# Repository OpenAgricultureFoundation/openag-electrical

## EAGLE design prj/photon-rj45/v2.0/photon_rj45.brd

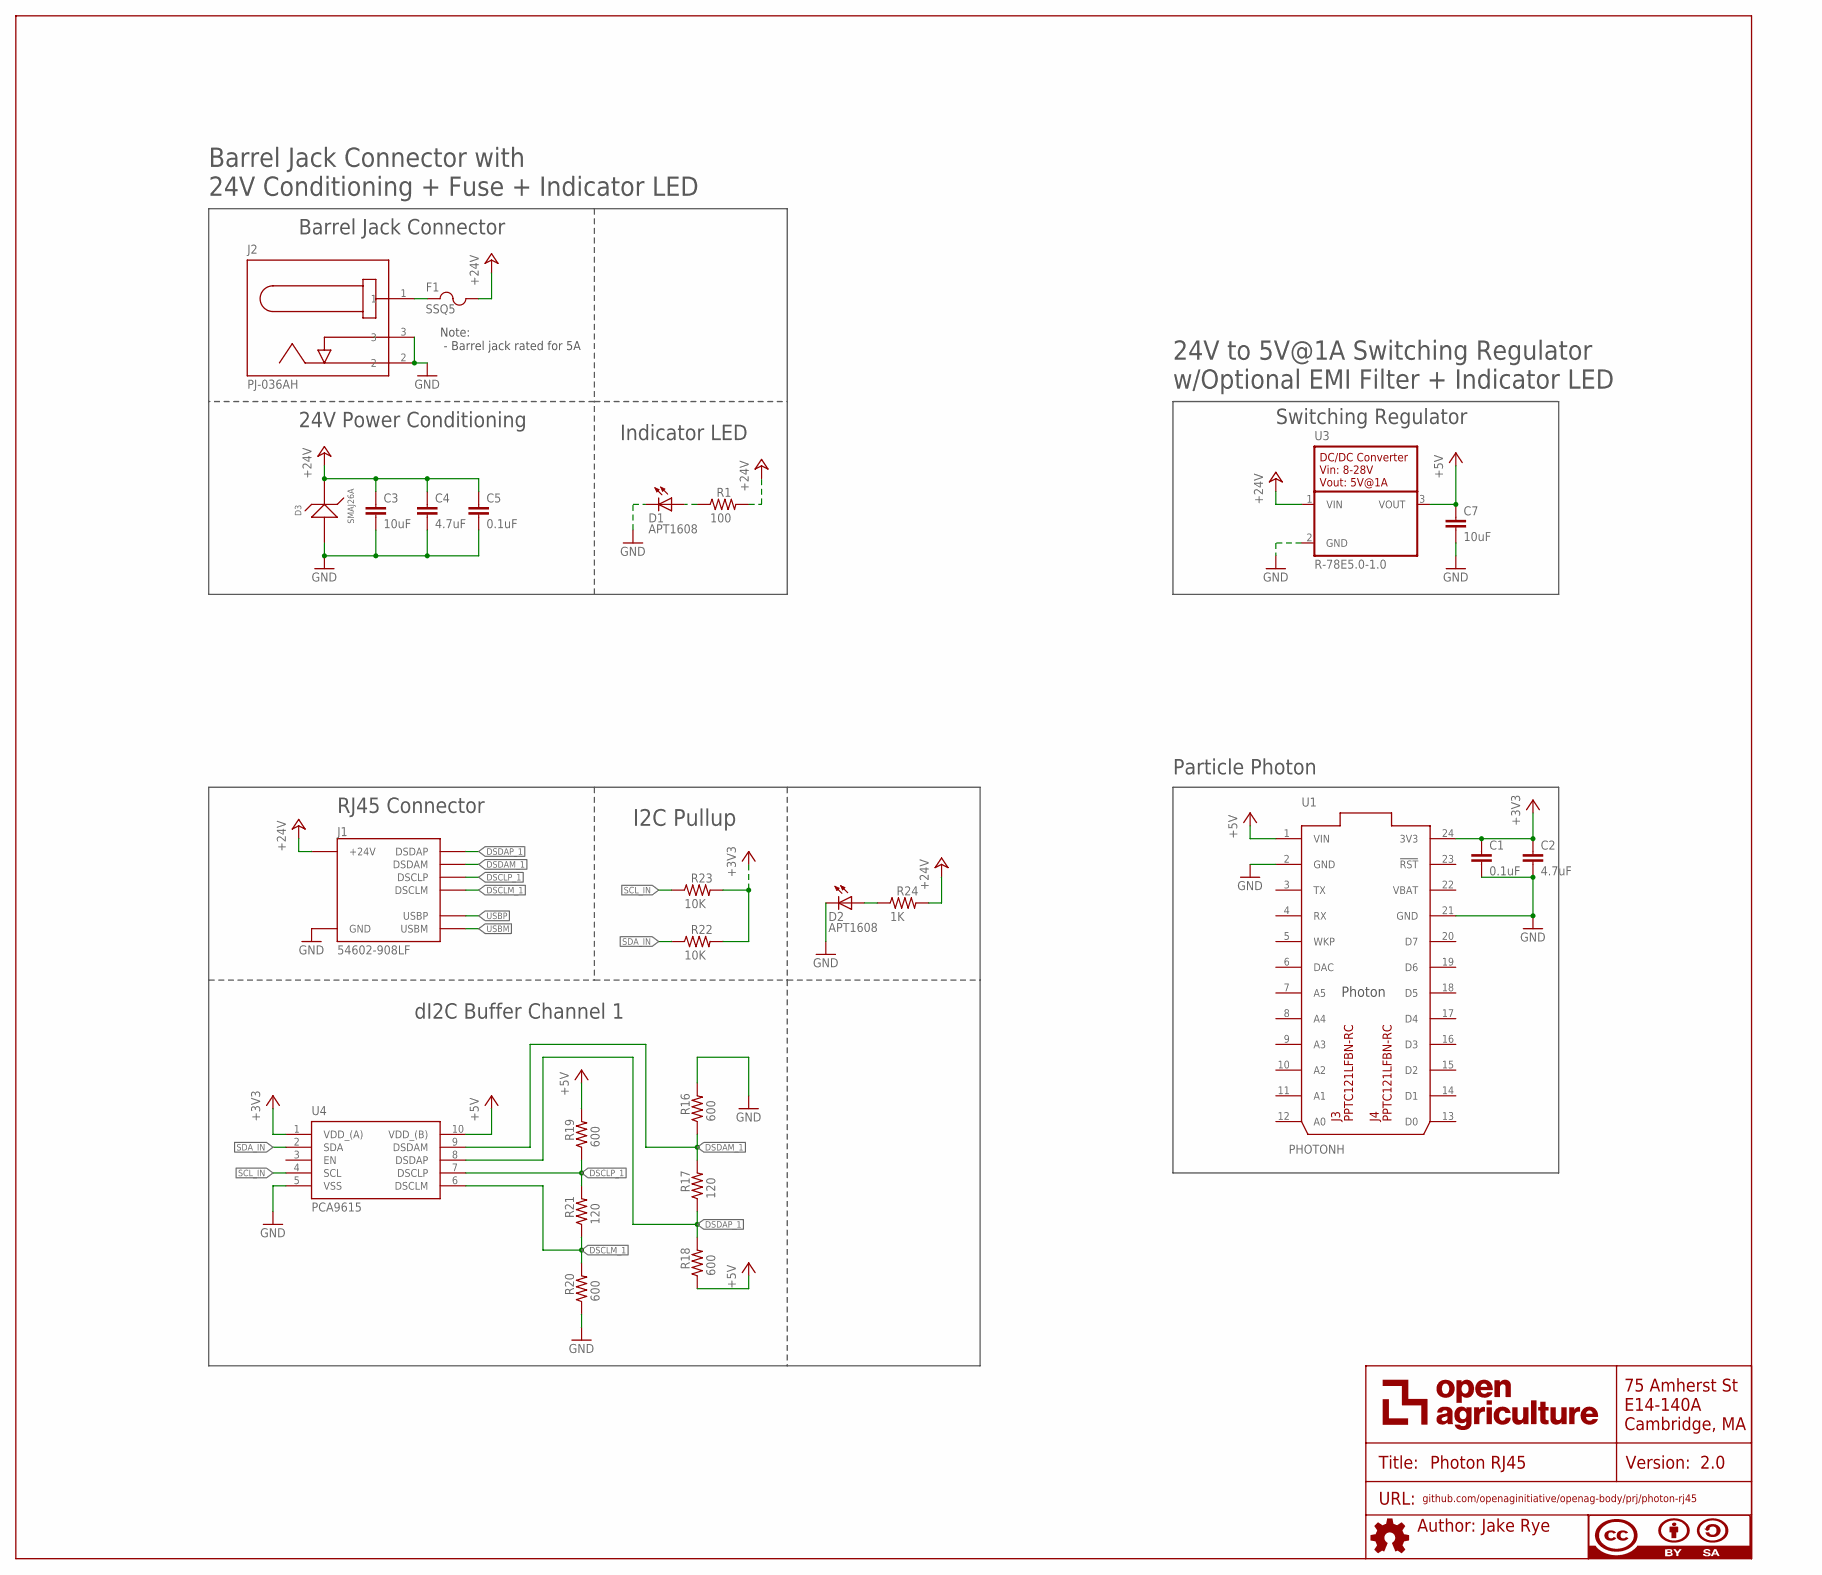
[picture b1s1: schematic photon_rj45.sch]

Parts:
C1, C5: 0.1uF; C0603
C2, C4: 4.7uF; C0805
C3, C7: 10uF; C0805
D1, D2: APT1608; CHIPLED_0603
D3: SMAJ26A; SMA
F1: SSQ5; SS
J1: 54602-908LF; RJ45-DI2C-USB-54602-908LF
J2: PJ-036AH; BARREL-JACK-PJ-036AH
J3, J4: PPTC121LFBN-RC; NAME-VALUE-ONLY
R1: 100; RC0603N
R16, R18, R19, R20: 600; RC0603N
R17, R21: 120; RC0603N
R22, R23: 10K; RC0603N
R24: 1K; RC0603N
U1: PHOTONH; PHOTON-NO-BOTTOM-LABELS
U3: R-78E5.0-1.0
U4: PCA9615; SOP50P490X110-10N

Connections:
24V_IN1: F1.1, J2.1
+3V3: C1.1, C2.1, R22.2, R23.2, U1.24 (3V3), U4.1 (VDD_(A))
+5V: C7.1, R18.1, R19.2, U1.1 (VIN), U3.3 (VOUT), U4.10 (VDD_(B))
+24V: C3.1, C4.1, C5.1, D3.1, F1.2, J1.24V(6) (+24V), R1.2, R24.2, U3.1 (VIN)
DSCLM_1: J1.DSCLM(5) (DSCLM), R20.2, R21.1, U4.6 (DSCLM)
DSCLP_1: J1.DSCLP(4) (DSCLP), R19.1, R21.2, U4.7 (DSCLP)
DSDAM_1: J1.DSDAM(2) (DSDAM), R16.1, R17.2, U4.9 (DSDAM)
DSDAP_1: J1.DSDAP(1) (DSDAP), R17.1, R18.2, U4.8 (DSDAP)
GND: C1.2, C2.2, C3.2, C4.2, C5.2, C7.2, D1.C, D2.C, D3.2, J1.GND(3) (GND), J2.2, J2.3, R16.2, R20.1, U1.2 (GND), U1.21 (GND), U3.2 (GND), U4.5 (VSS)
unnamed: D2.A, R24.1
unnamed: D1.A, R1.1
SCL_IN: R23.1, U4.4 (SCL)
SDA_IN: R22.1, U4.2 (SDA)
USBM: J1.USBM(8) (USBM)
USBP: J1.USBP(7) (USBP)
VBAT: U1.22 (VBAT)

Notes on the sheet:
dI2C Buffer Channel 1
RJ45 Connector
I2C Pullup
Barrel Jack Connector
Barrel Jack Connector with 24V Conditioning + Fuse + Indicator LED
24V Power Conditioning
Indicator LED
Note: - Barrel jack rated for 5A
24V to 5V@1A Switching Regulator w/Optional EMI Filter + Indicator LED
Switching Regulator
Particle Photon

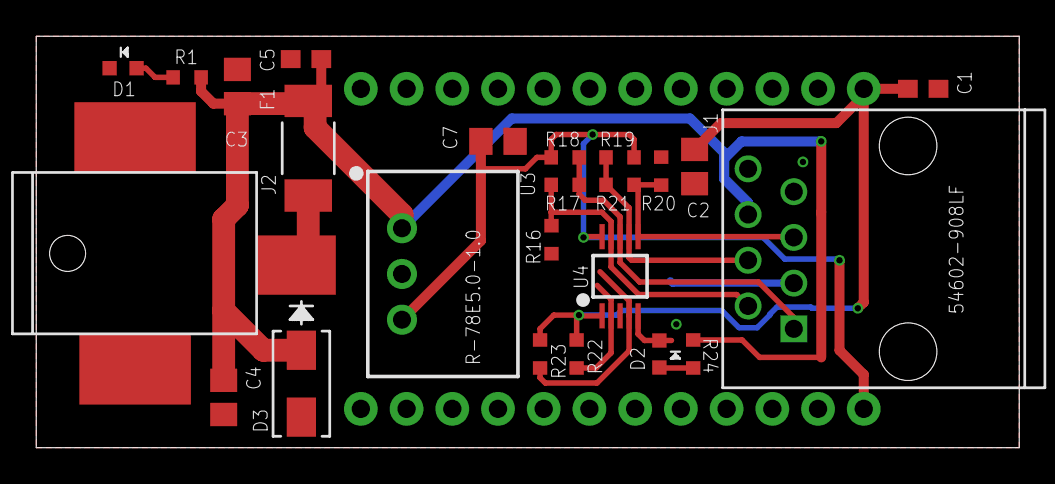
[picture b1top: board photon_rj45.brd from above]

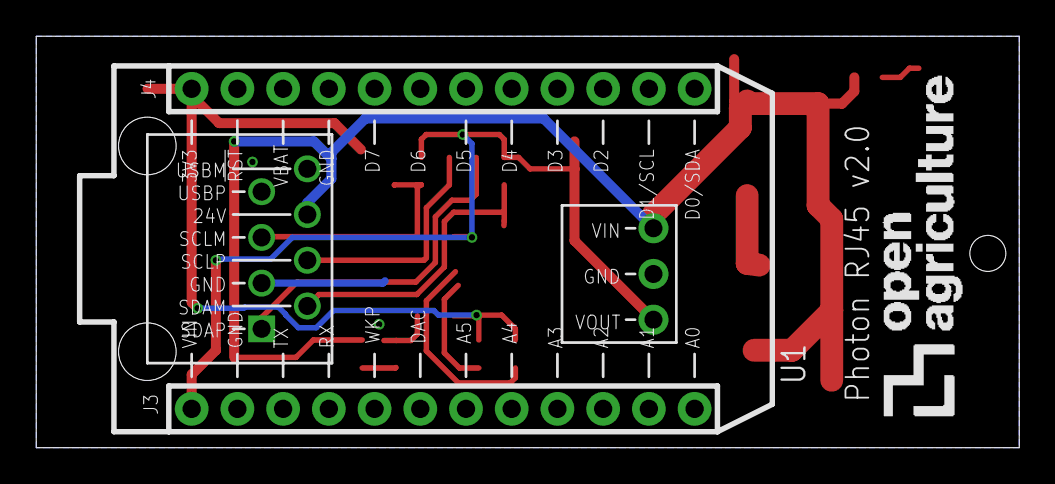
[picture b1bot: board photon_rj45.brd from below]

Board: 2 copper layers, 54.6 x 22.9 mm, 28 parts (4 on the bottom side), 13 nets.

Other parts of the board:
U$1: LOGO-BARE-750

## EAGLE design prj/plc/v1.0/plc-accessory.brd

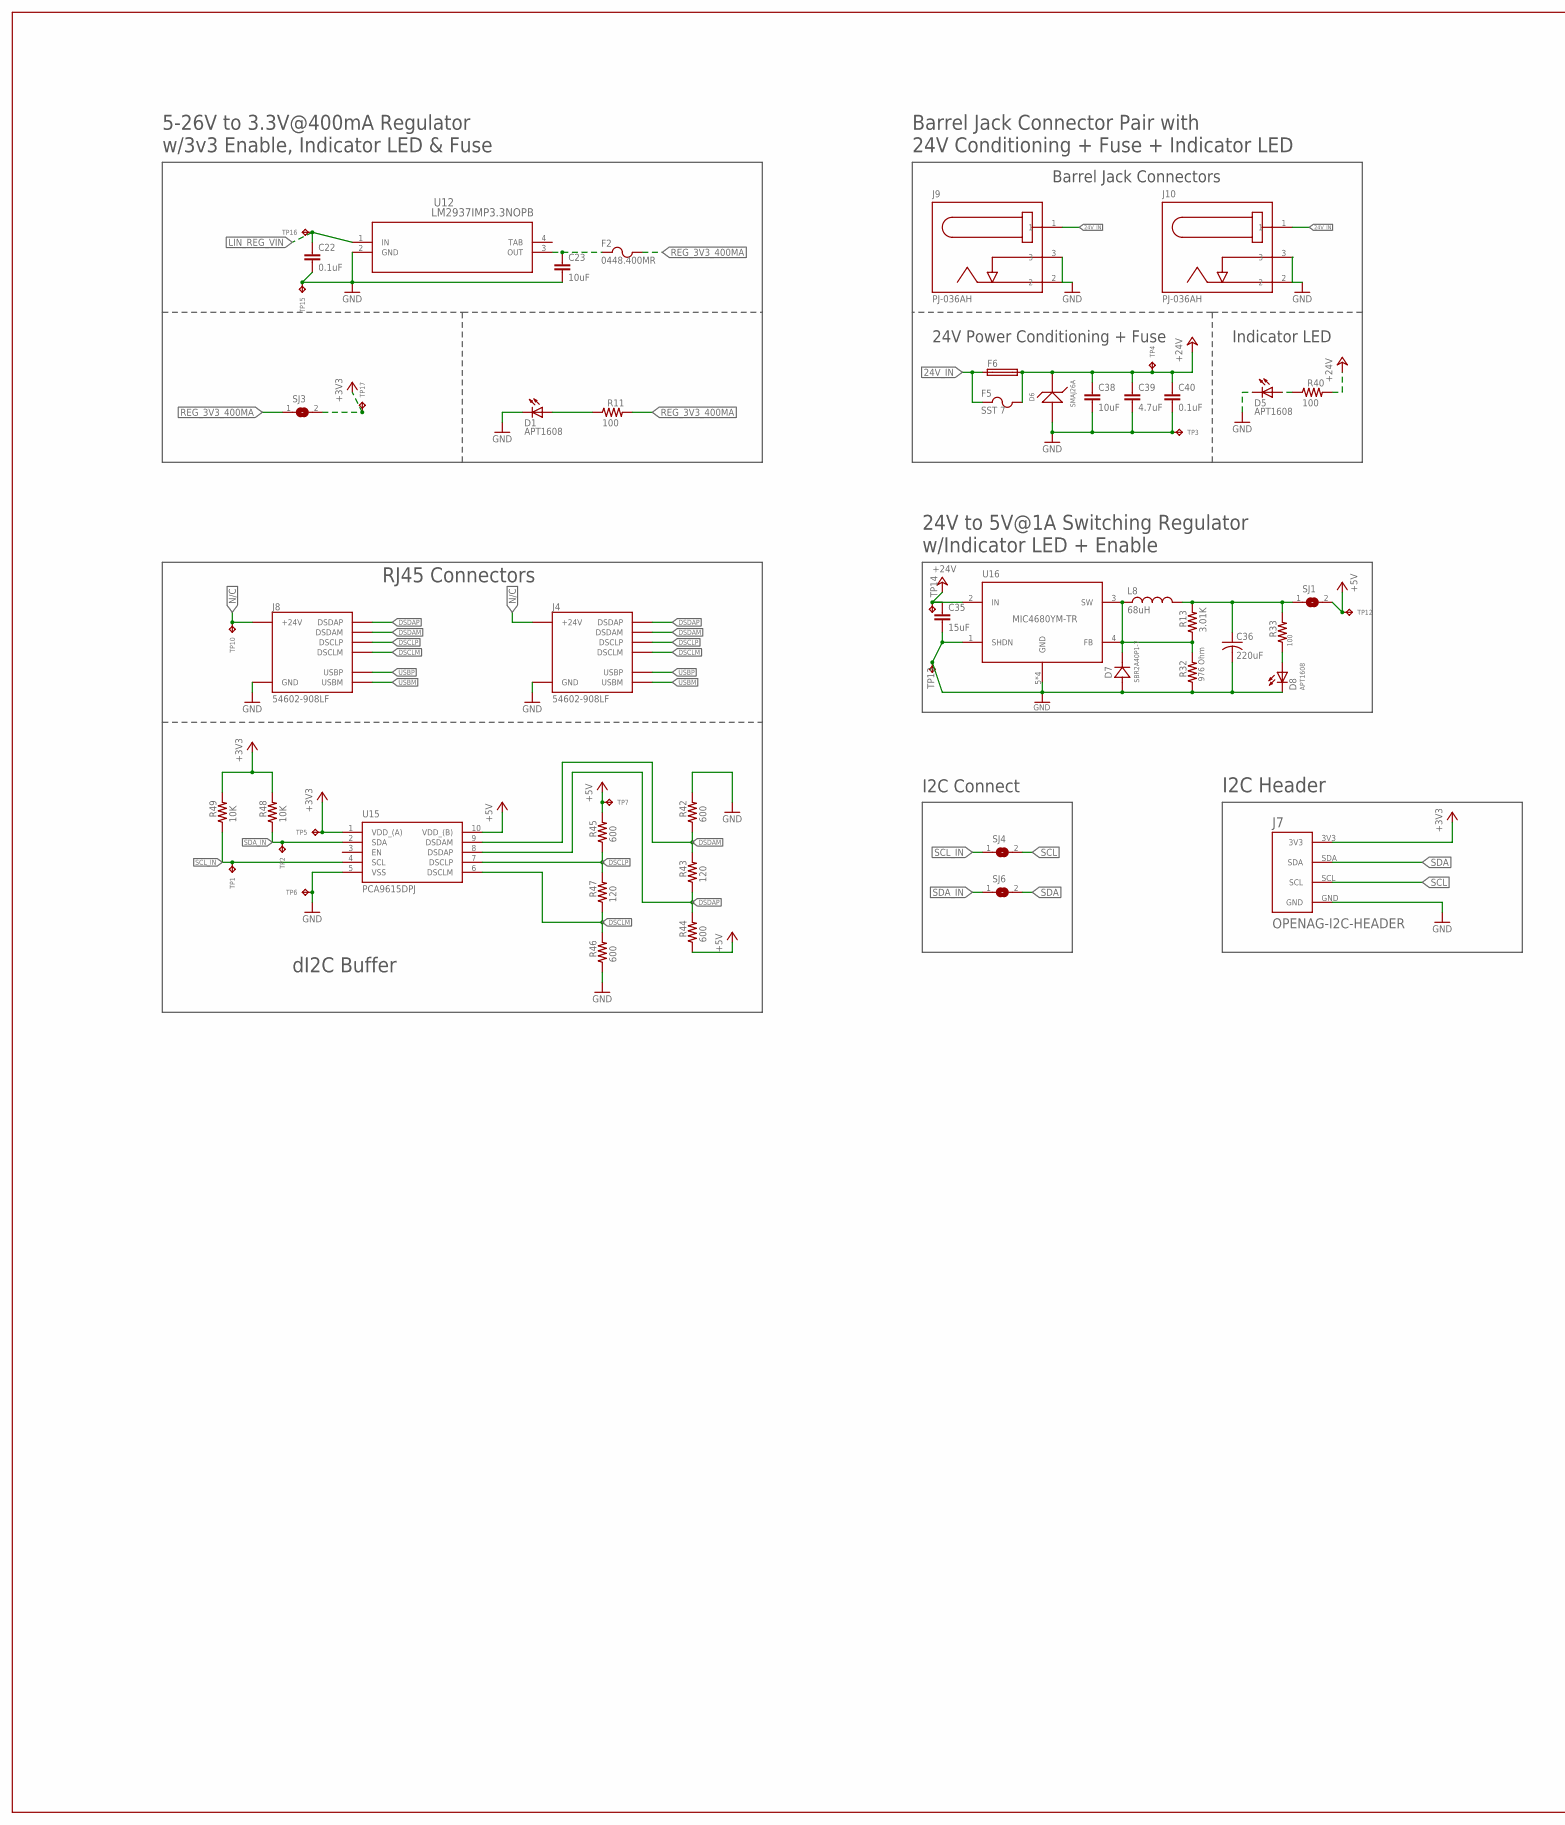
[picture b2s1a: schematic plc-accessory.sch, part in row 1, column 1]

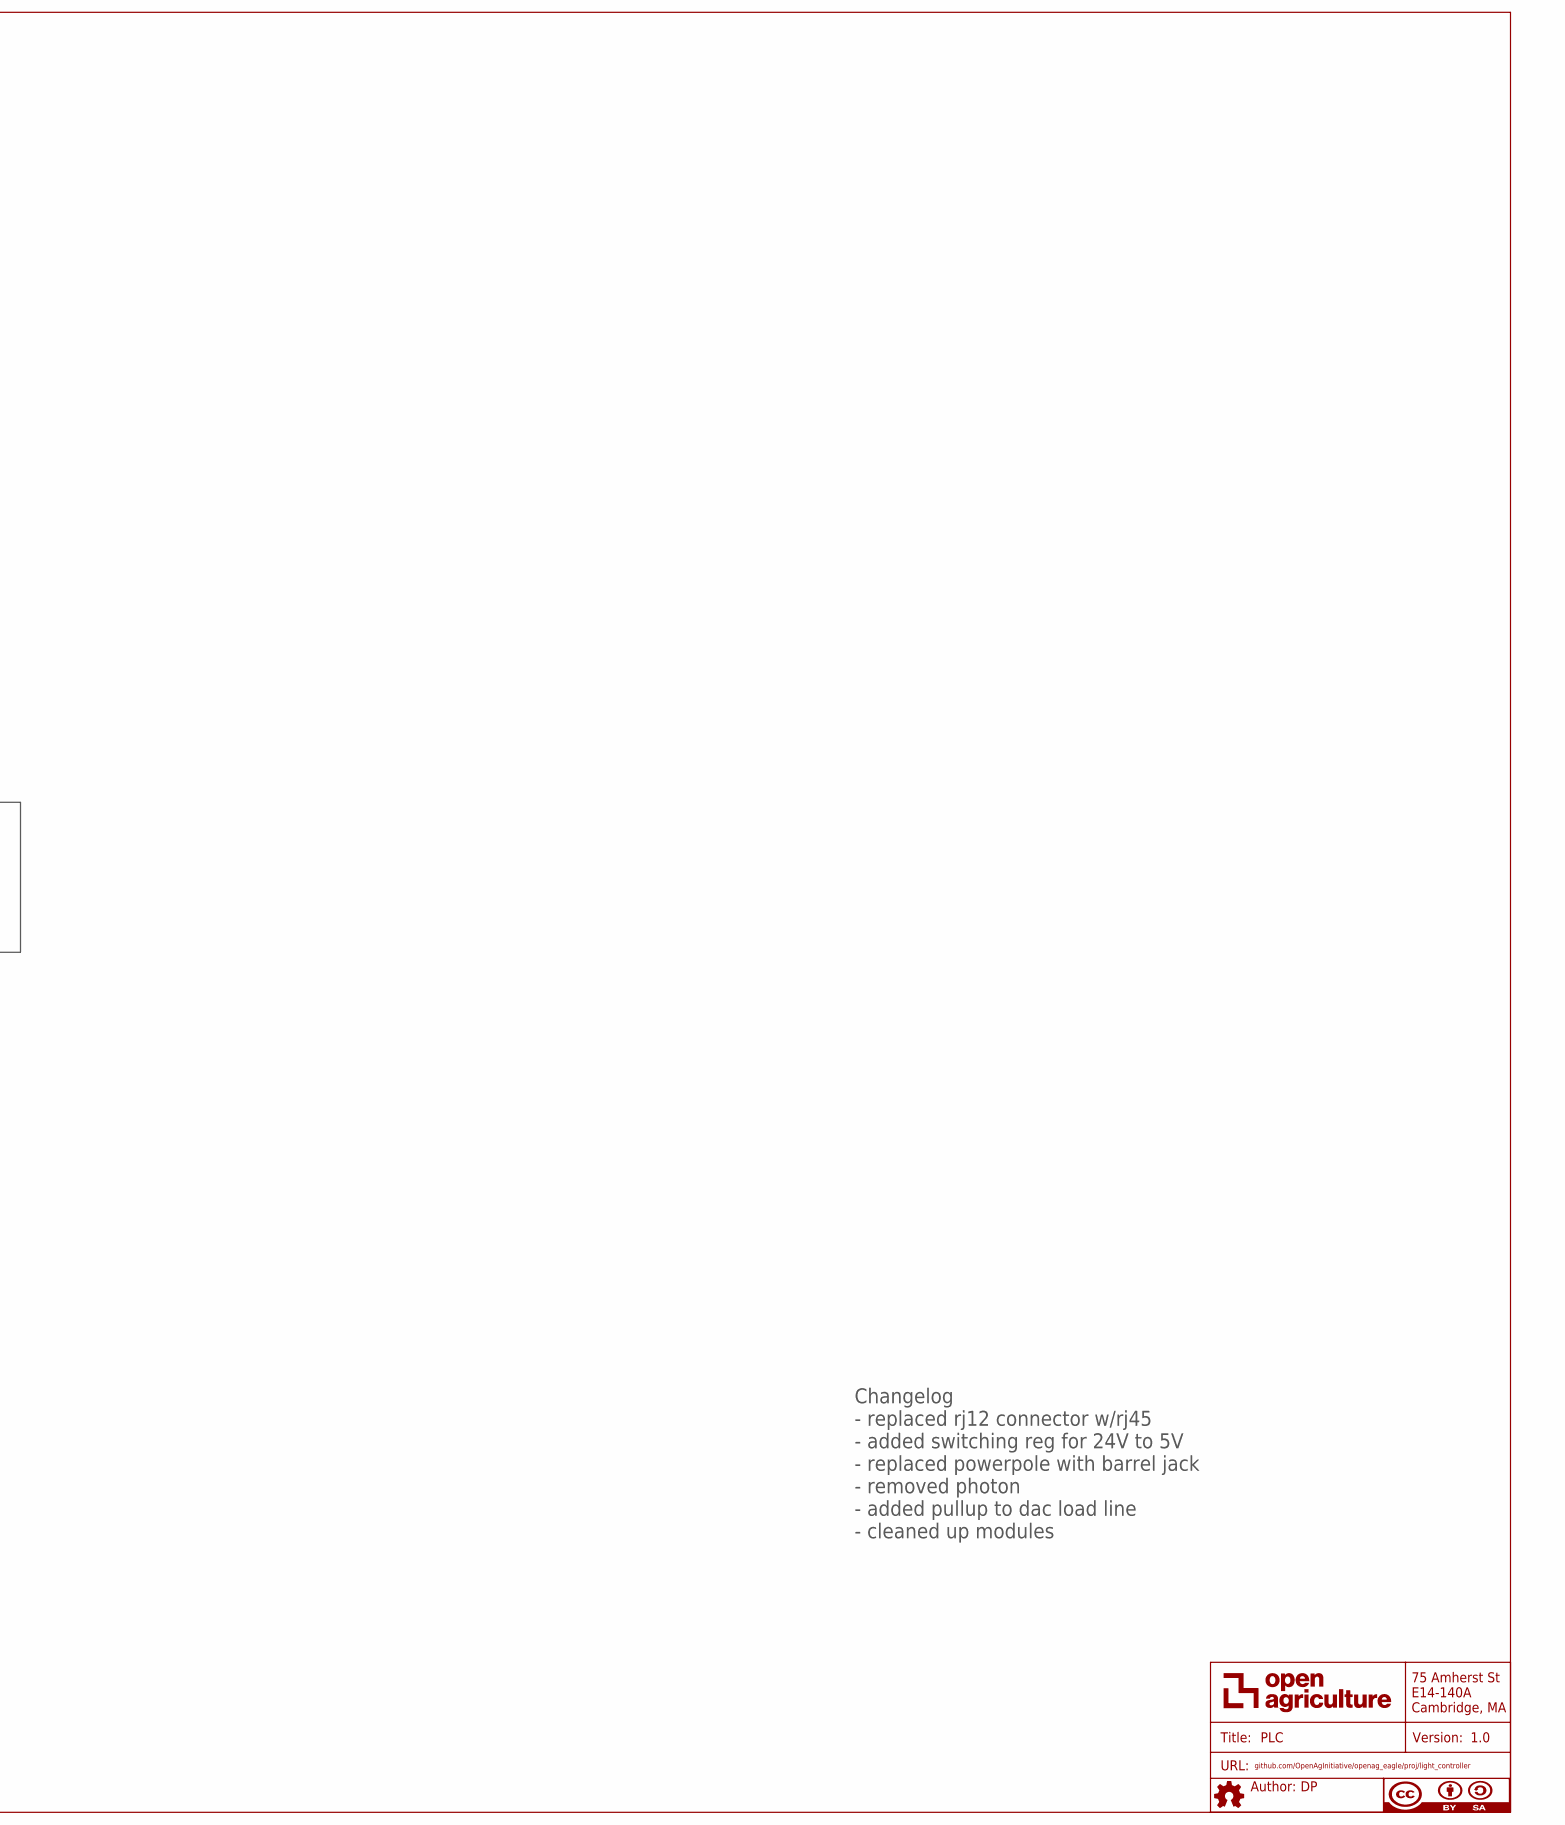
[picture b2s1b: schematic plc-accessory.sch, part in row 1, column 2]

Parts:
C22, C40: 0.1uF; C0603
C23, C38: 10uF; C0805
C35: 15uF; C0805
C36: 220uF; CT7343
C39: 4.7uF; C0805
D1, D5, D8: APT1608; CHIPLED_0603
D6: SMAJ26A; SMA
D7: SBR2A40P1-7; POWERDI123
F2: 0448.400MR; 0603
F5: SST 7; SS
F6: GSH15
FRAME1: DOCFIELD
J4, J8: 54602-908LF; OPENAG-V1-RJ45
J7: OPENAG-I2C-HEADER
J9, J10: PJ-036AH
L8: 68uH; UP2B
R11, R33, R40: 100; RC0603N
R13: 3.01K; RC0603N
R32: 976 Ohm; RC0603N
R42, R44, R45, R46: 600; RC0603N
R43, R47: 120; RC0603N
R48, R49: 10K; RC0603N
SJ1, SJ3, SJ4, SJ6: SOLDERJUMPERREFLOW_NOPASTE; SOLDERJUMPER_REFLOW_NOPASTE
TP1, TP2, TP3, TP4, TP5, TP6, TP7, TP10, TP12, TP13, TP14, TP15, TP16, TP17: TPTP06R; TP06R
U12: LM2937IMP3.3NOPB; MP04A
U15: PCA9615DPJ; SOP50P490X110-10N
U16: MIC4680YM-TR; SOIC8

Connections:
24V_IN: F5.1, F6.1, J9.1, J10.1
+3V3: J7.3V3, R48.2, R49.2, SJ3.2, TP5.TP, TP17.TP, U15.1 (VDD_(A))
+5V: R44.1, R45.2, SJ1.2, TP7.TP, TP12.TP, U15.10 (VDD_(B))
+24V: C35.1, C38.1, C39.1, C40.1, D6.1, F5.2, F6.2, R40.2, TP4.TP, TP14.TP, U16.2 (IN)
DSCLM: J4.DSCLM(5) (DSCLM), J8.DSCLM(5) (DSCLM), R46.2, R47.1, U15.6 (DSCLM)
DSCLP: J4.DSCLP(4) (DSCLP), J8.DSCLP(4) (DSCLP), R45.1, R47.2, U15.7 (DSCLP)
DSDAM: J4.DSDAM(2) (DSDAM), J8.DSDAM(2) (DSDAM), R42.1, R43.2, U15.9 (DSDAM)
DSDAP: J4.DSDAP(1) (DSDAP), J8.DSDAP(1) (DSDAP), R43.1, R44.2, U15.8 (DSDAP)
GND: C22.2, C23.2, C35.2, C36.- (2(-)), C38.2, C39.2, C40.2, D1.C, D5.C, D6.2, D7.- (21), D8.C, J4.GND(3) (GND), J7.GND, J8.GND(3) (GND), J9.2, J9.3, J10.2, J10.3, R32.1, R42.2, R46.1, TP3.TP, TP6.TP, TP13.TP, TP15.TP, U12.2 (GND), U15.5 (VSS), U16.1 (SHDN), U16.5 (GND), U16.6 (GND), U16.7 (GND), U16.8 (GND)
LIN_REG_VIN: C22.1, TP16.TP, U12.1 (IN)
unnamed: D1.A, R11.1
unnamed: D7.+ (12), L8.1, R13.1, R32.2, U16.3 (SW), U16.4 (FB)
unnamed: C23.1, F2.1, U12.3 (OUT)
unnamed: D8.A, R33.1
unnamed: C36.+ (1(+)), L8.2, R13.2, R33.2, SJ1.1
unnamed: D5.A, R40.1
N/C: J4.24V(6) (+24V), J8.24V(6) (+24V), TP10.TP
REG_3V3_400MA: F2.2, R11.2, SJ3.1
SCL: J7.SCL, SJ4.2
SCL_IN: R49.1, SJ4.1, TP1.TP, U15.4 (SCL)
SDA: J7.SDA, SJ6.2
SDA_IN: R48.1, SJ6.1, TP2.TP, U15.2 (SDA)
TAB: U12.4 (TAB)
USBM: J4.USBM(8) (USBM), J8.USBM(8) (USBM)
USBP: J4.USBP(7) (USBP), J8.USBP(7) (USBP)

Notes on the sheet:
I2C Header
Changelog - replaced rj12 connector w/rj45 - added switching reg for 24V to 5V - replaced powerpole with barrel jack - removed photon - added pullup to dac load line - cleaned up modules
Barrel Jack Connectors
Barrel Jack Connector Pair with 24V Conditioning + Fuse + Indicator LED
24V Power Conditioning + Fuse
Indicator LED
dI2C Buffer
RJ45 Connectors
24V to 5V@1A Switching Regulator w/Indicator LED + Enable
5-26V to 3.3V@400mA Regulator w/3v3 Enable, Indicator LED & Fuse
I2C Connect

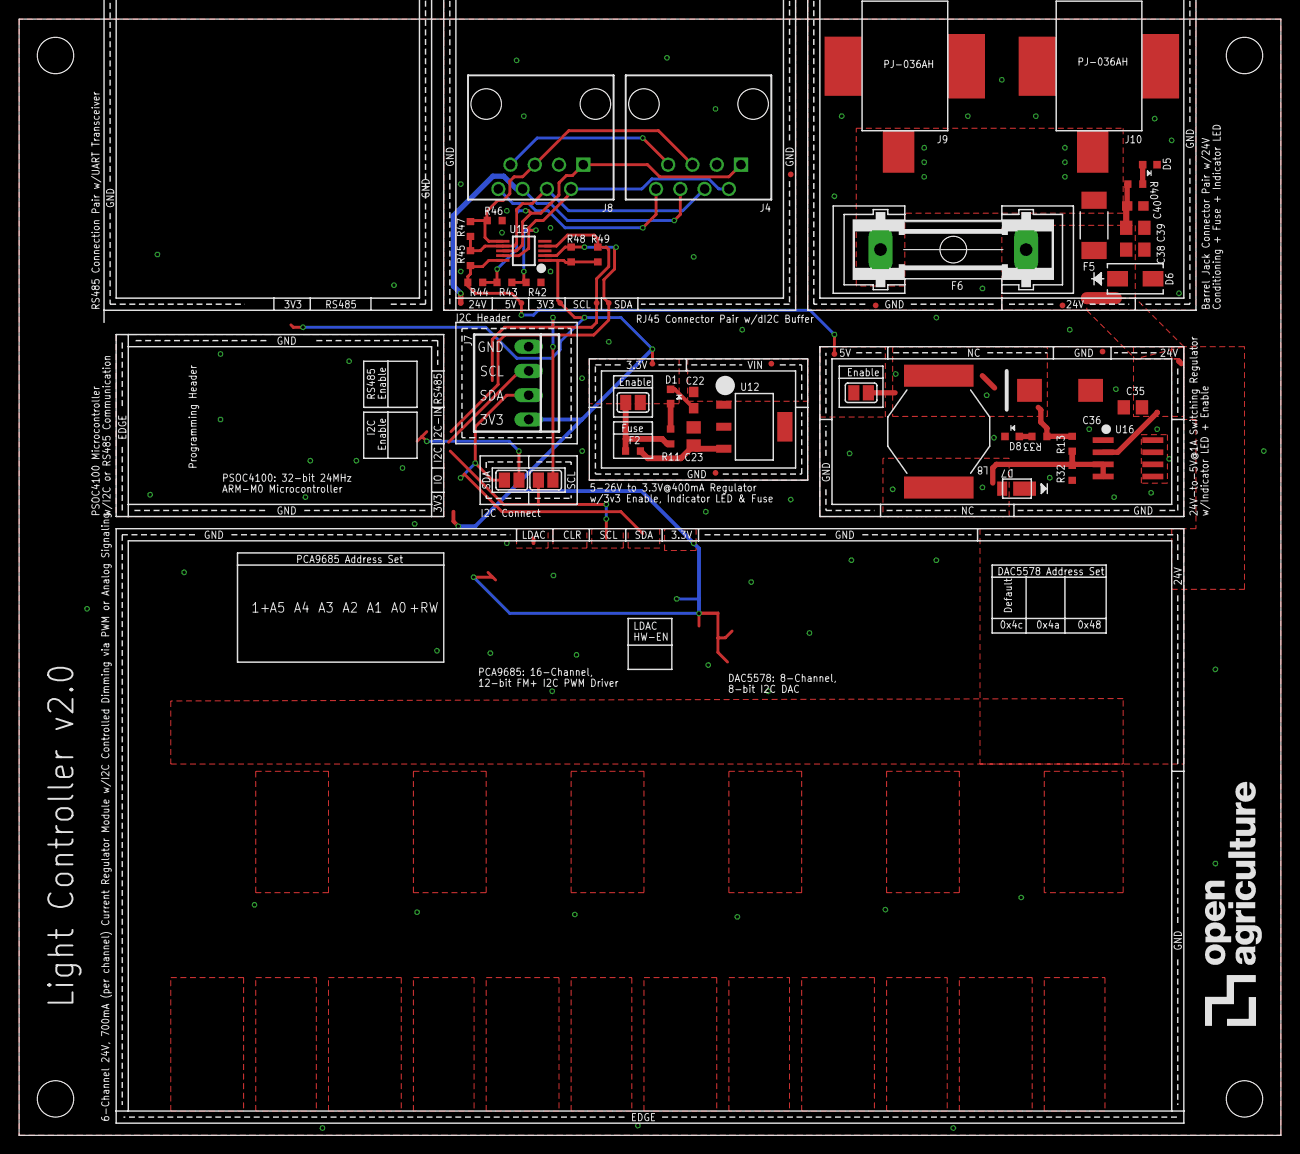
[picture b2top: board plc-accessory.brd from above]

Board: 2 copper layers, 132.1 x 116.8 mm, 61 parts (1 on the bottom side), 24 nets.

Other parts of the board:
U$1, U$2, U$3, U$4: OPENAG-CORNER-MOUNTING-HOLE
U$5: OPENAG-LOGO-1000-MIL

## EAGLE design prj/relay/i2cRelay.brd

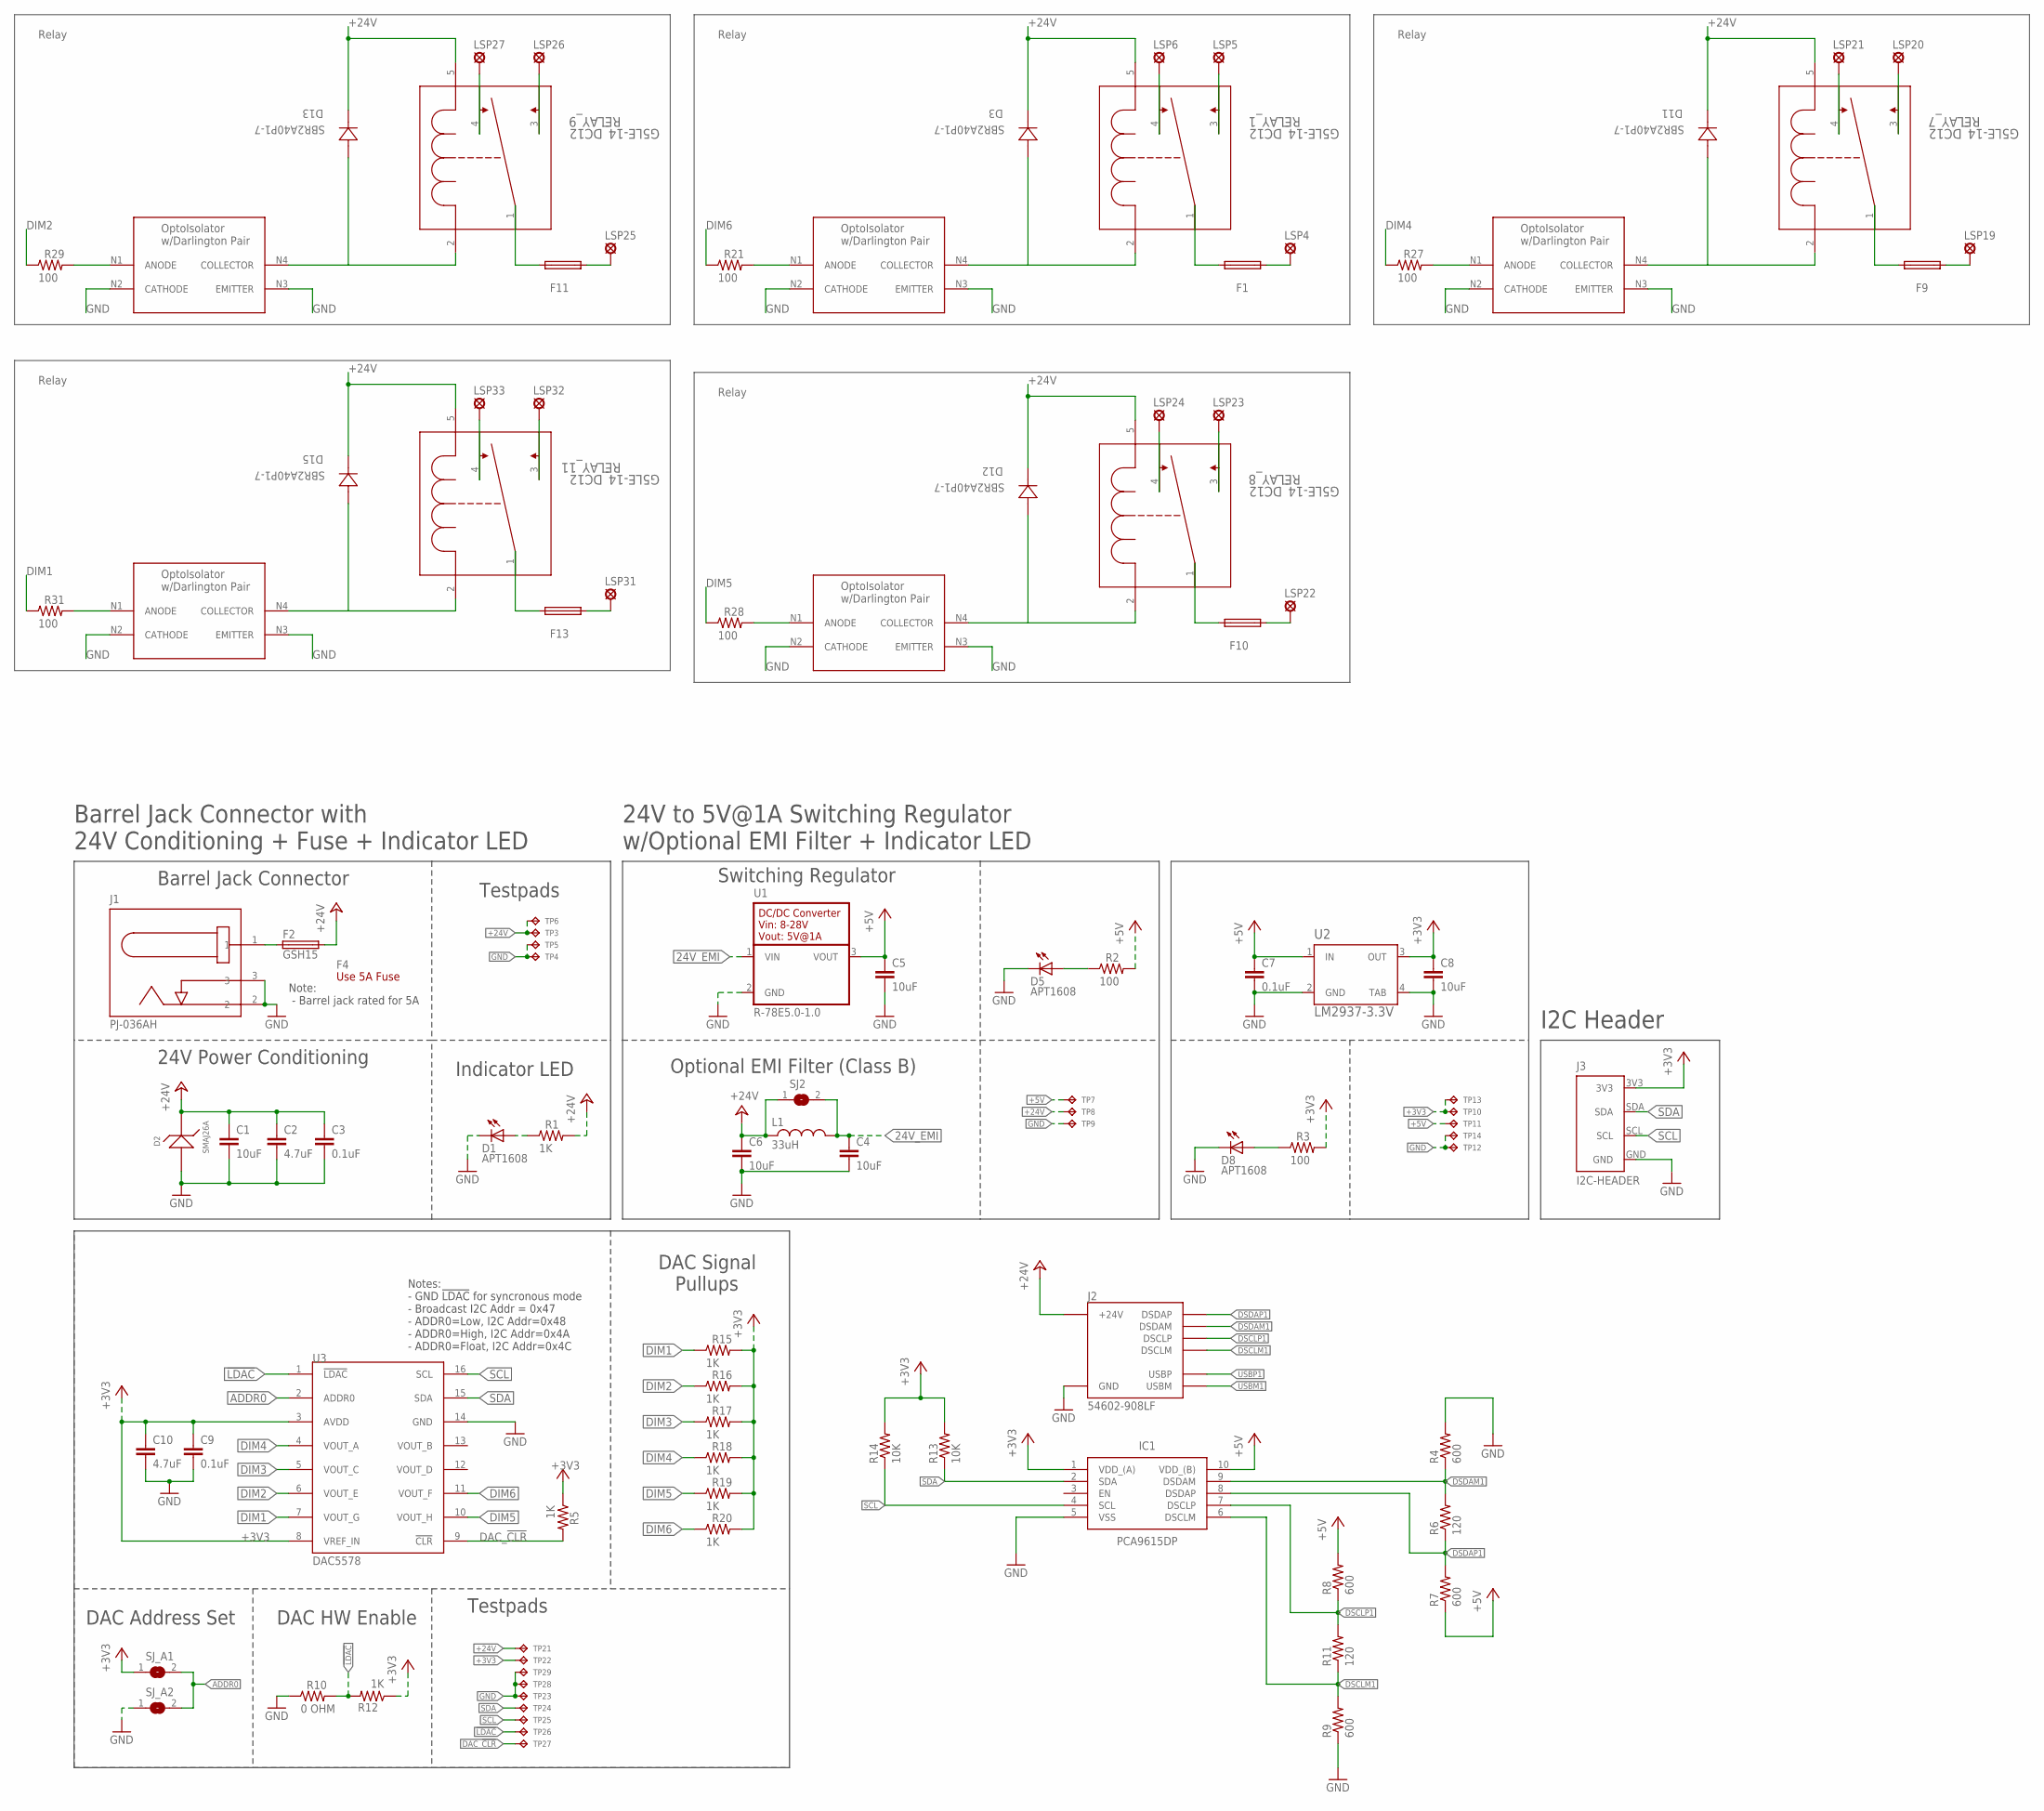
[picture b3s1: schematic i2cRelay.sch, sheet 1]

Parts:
C1, C4, C5, C6, C8: 10uF; C0805
C2, C10: 4.7uF; C0805
C3, C7, C9: 0.1uF; C0603
D1, D5, D8: APT1608; CHIPLED_0603
D2: SMAJ26A; SMA
D3, D11, D12, D13, D15: SBR2A40P1-7; POWERDI123
F1, F2, F9, F10, F11, F13: GSH15
F4: Use 5A Fuse; FUSE-CARTRIDGE
IC1: PCA9615DP; SOP50P490X110-10N
J1: PJ-036AH; BARREL-JACK-PJ-036AH
J2: 54602-908LF; OPENAG-V1-RJ45
J3: I2C-HEADER; HEADER-I2C
L1: 33uH; 29333C
LSP4, LSP5, LSP6, LSP19, LSP20, LSP21, LSP22, LSP23, LSP24, LSP25, LSP26, LSP27, LSP31, LSP32, LSP33: SE14
R1, R5, R12, R15, R16, R17, R18, R19, R20: 1K; RC0603N
R2, R3, R21, R27, R28, R29, R31: 100; RC0603N
R4, R7, R8, R9: 600; R0603
R6, R11: 120; R0603
R10: 0 OHM; RC0603N
R13, R14: 10K; R0603
RELAY_1, RELAY_7, RELAY_8, RELAY_9, RELAY_11: G5LE-14_DC12; RELAY_G5LE-1
SJ2: EMI-BYPASS
SJ_A1, SJ_A2: SOLDERJUMPERREFLOW_NOPASTE; SJ1
TP3, TP4, TP5, TP6, TP10, TP11, TP12, TP13, TP14, TP21, TP22, TP23, TP24, TP25, TP26, TP27, TP28, TP29: TPTP04R; TP04R
TP7, TP8, TP9: TPTP06R; TP06R
U1: R-78E5.0-1.0
U2: LM2937-3.3V; MP04A
U3: DAC5578; TSSOP16
U$3, U$8, U$9, U$10, U$12: LTV-355T

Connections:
24V_EMI: C4.1, L1.2, SJ2.2, U1.1 (VIN)
24V_IN1: F2.1, J1.1
!LDAC!: R10.2, R12.2, TP26.1, U3.1 (!LDAC!)
+3V3: C8.1, C9.1, C10.1, IC1.1 (VDD_(A)), J3.3V3, R3.2, R5.1, R12.1, R13.2, R14.2, R15.2, R16.2, R17.2, R18.2, R19.2, R20.2, SJ_A1.1, TP10.1, TP13.1, TP22.1, U2.3 (OUT), U3.3 (AVDD), U3.8 (VREF_IN)
+5V: C5.1, C7.1, IC1.10 (VDD_(B)), R2.2, R7.1, R8.2, TP7.TP, TP11.1, U1.3 (VOUT), U2.1 (IN)
+24V: C1.1, C2.1, C3.1, C6.1, D2.1, D3.-, D11.-, D12.-, D13.-, D15.-, F2.2, J2.24V(6) (+24V), L1.1, R1.2, RELAY_1.5, RELAY_7.5, RELAY_8.5, RELAY_9.5, RELAY_11.5, SJ2.1, TP3.1, TP6.1, TP8.TP, TP21.1; also elsewhere on the board
ADDR0: SJ_A1.2, SJ_A2.2, U3.2 (ADDR0)
DAC_!CLR!: R5.2, TP27.1, U3.9 (!CLR!)
DIM1: R15.1, R31.1, U3.7 (VOUT_G)
DIM2: R16.1, R29.1, U3.6 (VOUT_E)
DIM3: R17.1, U3.5 (VOUT_C); also elsewhere on the board
DIM4: R18.1, R27.1, U3.4 (VOUT_A)
DIM5: R19.1, R28.1, U3.10 (VOUT_H)
DIM6: R20.1, R21.1, U3.11 (VOUT_F)
DSCLM1: IC1.6 (DSCLM), J2.DSCLM(5) (DSCLM), R9.2, R11.1
DSCLP1: IC1.7 (DSCLP), J2.DSCLP(4) (DSCLP), R8.1, R11.2
DSDAM1: IC1.9 (DSDAM), J2.DSDAM(2) (DSDAM), R4.1, R6.2
DSDAP1: IC1.8 (DSDAP), J2.DSDAP(1) (DSDAP), R6.1, R7.2
GND: C1.2, C2.2, C3.2, C4.2, C5.2, C6.2, C7.2, C8.2, C9.2, C10.2, D1.C, D2.2, D5.C, D8.C, IC1.5 (VSS), J1.2, J1.3, J2.GND(3) (GND), J3.GND, R4.2, R9.1, R10.1, SJ_A2.1, TP4.1, TP5.1, TP9.TP, TP12.1, TP14.1, TP23.1, TP28.1, TP29.1, U1.2 (GND), U2.2 (GND), U2.4 (TAB), U3.14 (GND), U$3.N2 (CATHODE), U$3.N3 (EMITTER), U$8.N2 (CATHODE), U$8.N3 (EMITTER), U$9.N2 (CATHODE), U$9.N3 (EMITTER), U$10.N2 (CATHODE), U$10.N3 (EMITTER), U$12.N2 (CATHODE), U$12.N3 (EMITTER); also elsewhere on the board
unnamed: D1.A, R1.1
unnamed: D5.A, R2.1
unnamed: D3.+, RELAY_1.2 (1), U$3.N4 (COLLECTOR)
unnamed: D8.A, R3.1
unnamed: F1.2, RELAY_1.1 (2)
unnamed: LSP5.MP, RELAY_1.3
unnamed: R21.2, U$3.N1 (ANODE)
unnamed: LSP6.MP, RELAY_1.4
unnamed: F1.1, LSP4.MP
unnamed: D11.+, RELAY_7.2 (1), U$8.N4 (COLLECTOR)
unnamed: F9.2, RELAY_7.1 (2)
unnamed: LSP20.MP, RELAY_7.3
unnamed: R27.2, U$8.N1 (ANODE)
unnamed: LSP21.MP, RELAY_7.4
unnamed: F9.1, LSP19.MP
unnamed: D12.+, RELAY_8.2 (1), U$9.N4 (COLLECTOR)
unnamed: F10.2, RELAY_8.1 (2)
unnamed: LSP23.MP, RELAY_8.3
unnamed: R28.2, U$9.N1 (ANODE)
unnamed: LSP24.MP, RELAY_8.4
unnamed: F10.1, LSP22.MP
unnamed: D13.+, RELAY_9.2 (1), U$10.N4 (COLLECTOR)
unnamed: F11.2, RELAY_9.1 (2)
unnamed: LSP26.MP, RELAY_9.3
unnamed: R29.2, U$10.N1 (ANODE)
unnamed: LSP27.MP, RELAY_9.4
unnamed: F11.1, LSP25.MP
unnamed: D15.+, RELAY_11.2 (1), U$12.N4 (COLLECTOR)
unnamed: F13.2, RELAY_11.1 (2)
unnamed: LSP32.MP, RELAY_11.3
unnamed: R31.2, U$12.N1 (ANODE)
unnamed: LSP33.MP, RELAY_11.4
unnamed: F13.1, LSP31.MP
SCL: IC1.4 (SCL), J3.SCL, R14.1, TP25.1, U3.16 (SCL)
SDA: IC1.2 (SDA), J3.SDA, R13.1, TP24.1, U3.15 (SDA)
USBM1: J2.USBM(8) (USBM)
USBP1: J2.USBP(7) (USBP)

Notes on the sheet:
Barrel Jack Connector
Barrel Jack Connector with 24V Conditioning + Fuse + Indicator LED
24V Power Conditioning
Indicator LED
Testpads
Note: - Barrel jack rated for 5A
24V to 5V@1A Switching Regulator w/Optional EMI Filter + Indicator LED
Switching Regulator
Optional EMI Filter (Class B)
Notes: - GND !LDAC! for syncronous mode - Broadcast I2C Addr = 0x47 - ADDR0=Low, I2C Addr=0x48 - ADDR0=High, I2C Addr=0x4A - ADDR0=Float, I2C Addr=0x4C
DAC Signal Pullups
DAC Address Set
DAC HW Enable
I2C Header
Relay

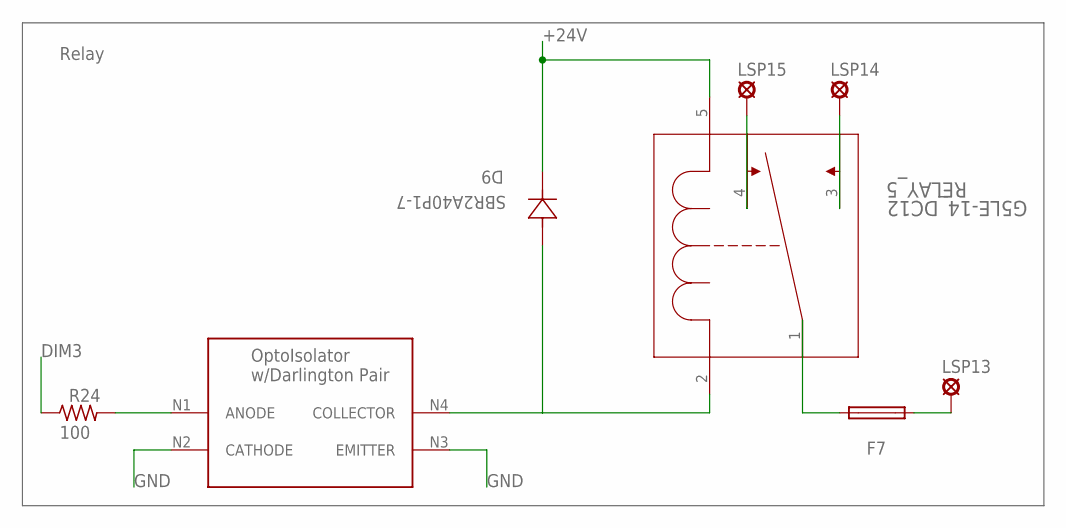
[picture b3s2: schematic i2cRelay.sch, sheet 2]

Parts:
D9: SBR2A40P1-7; POWERDI123
F7: GSH15
LSP13, LSP14, LSP15: SE14
R24: 100; RC0603N
RELAY_5: G5LE-14_DC12; RELAY_G5LE-1
U$6: LTV-355T

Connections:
+24V: D9.-, RELAY_5.5; also elsewhere on the board
DIM3: R24.1; also elsewhere on the board
GND: U$6.N2 (CATHODE), U$6.N3 (EMITTER); also elsewhere on the board
unnamed: D9.+, RELAY_5.2 (1), U$6.N4 (COLLECTOR)
unnamed: F7.2, RELAY_5.1 (2)
unnamed: LSP14.MP, RELAY_5.3
unnamed: R24.2, U$6.N1 (ANODE)
unnamed: LSP15.MP, RELAY_5.4
unnamed: F7.1, LSP13.MP

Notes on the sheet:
Relay
